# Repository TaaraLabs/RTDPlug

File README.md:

RTD Plug
========

[WebSite](https://taaralabs.eu/rp1)

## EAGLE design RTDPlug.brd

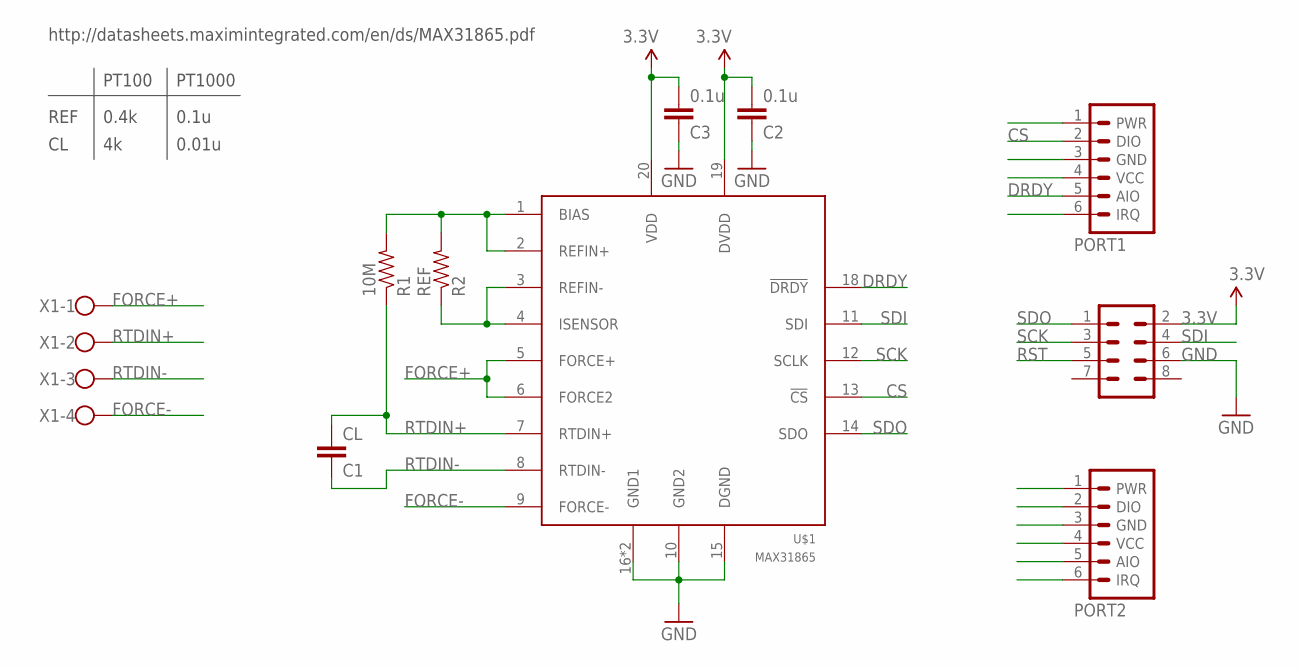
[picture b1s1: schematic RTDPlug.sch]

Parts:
C1: CL; 0603-CAP
C2, C3: 0.1u; 0603-CAP
ISP: MA04-2
PORT1, PORT2: JEEPORT-FEMALE; 1X06_FEMALE_LOCK.010
R1: 10M; 0603-RES
R2: REF; 1206
U$1: MAX31865; TQFN20-5X5
X1: W237-4

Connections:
3.3V: C2.2, C3.2, ISP.2, U$1.19 (DVDD), U$1.20 (VDD)
CS: PORT1.2 (DIO), U$1.13 (!CS)
DRDY: PORT1.5 (AIO), U$1.18 (!DRDY)
FORCE+: U$1.5 (FORCE+), U$1.6 (FORCE2), X1.1
FORCE-: U$1.9 (FORCE-), X1.4
GND: C2.1, C3.1, ISP.6, U$1.10 (GND2), U$1.15 (DGND), U$1.16 (GND1), U$1.EXP (GND1)
unnamed: R1.2, R2.2, U$1.1 (BIAS), U$1.2 (REFIN+)
unnamed: R2.1, U$1.3 (REFIN-), U$1.4 (ISENSOR)
RST: ISP.5
RTDIN+: C1.2, R1.1, U$1.7 (RTDIN+), X1.2
RTDIN-: C1.1, U$1.8 (RTDIN-), X1.3
SCK: ISP.3, U$1.12 (SCLK)
SDI: ISP.4, U$1.11 (SDI)
SDO: ISP.1, U$1.14 (SDO)

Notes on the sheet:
http://datasheets.maximintegrated.com/en/ds/MAX31865.pdf
REF
PT100
PT1000
0.4k
0.1u
0.01u

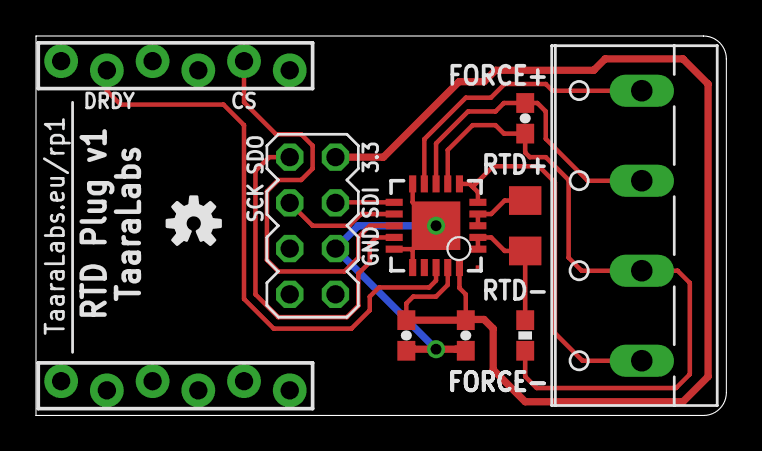
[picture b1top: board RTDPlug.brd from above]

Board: 2 copper layers, 38.4 x 21.1 mm, 12 parts (1 on the bottom side), 13 nets.

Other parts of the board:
U$2, U$3: OSHW-LOGO-S

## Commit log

2015-02-01 :confetti_ball: Added .gitattributes & .gitignore files
2015-02-01 RTDPlug

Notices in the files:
parts and their libraries:
SparkFun: Licensing: CC v3.0 Share-Alike You are welcome to use this library for commercial purposes.
